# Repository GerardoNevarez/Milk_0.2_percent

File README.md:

# Milk 0.2 percent

Remix from the [2% Milk](https://github.com/Spaceboards/SpaceboardsHardware/blob/master/Keyboards/2%25%20Milk/milk_kicad.zip) by Spaceman

# BOM

- 1 - Molex 2171800001 USB-C connector [Mouser](https://www.mouser.com/ProductDetail/Molex/217180-0001?qs=DRkmTr78QAS4XYOWSgPndA%3D%3D)
- 1 - SOIC-8 ATtiny85 - [ATTINY85-20SU](https://www.mouser.com/ProductDetail/Microchip-Technology-Atmel/ATTINY85-20SU?qs=sGAEpiMZZMsJEQNpvQJiZ7QX9auzN2X%252B) 
- 1 - 0805 0.1uF ceramic cap
- 1 - 0805 4.7uF ceramic cap
- 1 - 0805 1.5k omh resistor
- 2 - 0805 5.1k omh resistors
- 2 - 0805 68 omh resistors
- 1 - 1206 500ma PolyFuse
- 2 - 0805 3.6V Zener diodes
- 1 - (optional) 6x3mm THT temporary push switch (Reset)
- 2 - (optional) 1515 RGB leds - SK6805-EC-15 [Adafruit](https://www.adafruit.com/product/4492)

Use the front and back PCB renders, to locate the location for the parts

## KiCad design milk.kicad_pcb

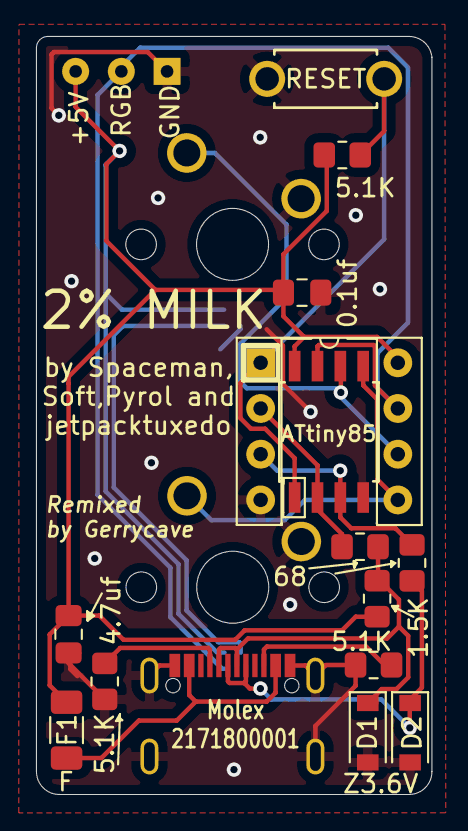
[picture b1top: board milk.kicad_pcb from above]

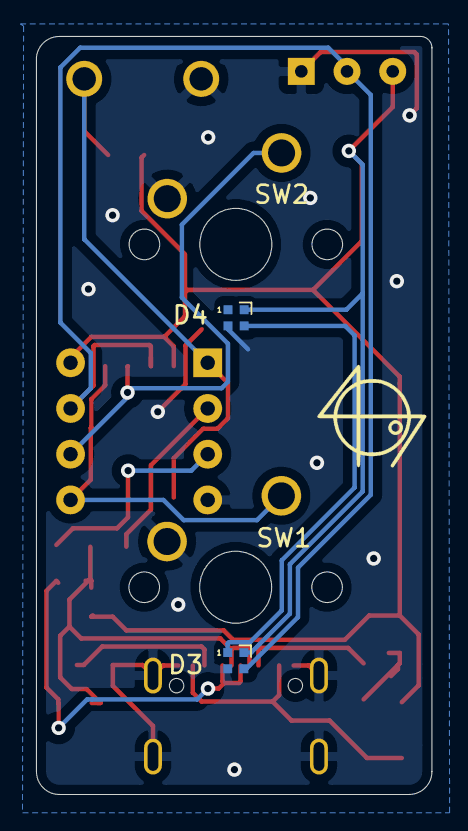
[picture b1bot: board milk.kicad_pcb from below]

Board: 2 copper layers, 22.0 x 42.1 mm, 20 parts (4 on the bottom side), 14 nets.

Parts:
C1: 0.1uf; C_0805_2012Metric_Pad1.18x1.45mm_HandSolder
C2: 4.7uf; C_0805_2012Metric_Pad1.18x1.45mm_HandSolder
D1, D2: 3.6V; D_SOD-123
D3, D4: SK6805; LED_SK6812_EC15_1.5x1.5mm
F1: Polyfuse; R_1206_3216Metric_Pad1.30x1.75mm_HandSolder
J1: USB_C_Receptacle_USB2.0; Molex_2171800001
J2: RGB; PinHeader_1x03_P2.54mm_Vertical
J3: DIP-8 Socket; DIP-8_W7.62mm_Socket
R1, R2, R6: 5.1K; R_0805_2012Metric_Pad1.20x1.40mm_HandSolder
R3, R4: 68; R_0805_2012Metric_Pad1.20x1.40mm_HandSolder
R5: 1.5K; R_0805_2012Metric_Pad1.20x1.40mm_HandSolder
SW1, SW2: SW_Push; SW_Cherry_MX_1.00u_PCB-2mm
SW3: SW_Push_Reset; ResetSW_1side
U1: ATtiny85-20SU; SOIJ-8_5.3x5.3mm_P1.27mm

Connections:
+5V: C1.1, C2.2, D3.4, D4.4, F1.1, J2.3, J3.8, R5.1, R6.2, U1.8
D+: D2.1, J1.A6, J1.B6, R4.2
D-: D1.1, J1.A7, J1.B7, R3.2, R5.2
GND: C1.2, C2.1, D1.2, D2.2, D3.2, D4.2, J1.A1, J1.B1, J1.S1, J2.1, J3.4, R1.1, R2.1, SW1.2, SW2.2, SW3.2, U1.4
unnamed: D3.1, D4.3
unnamed: J1.A5, R1.2
unnamed: J1.B5, R2.2
PB0: J3.5, SW1.1, U1.5
PB1: J3.6, SW2.1, U1.6
PB3: J3.2, R3.1, U1.2
PB4: J3.3, R4.1, U1.3
RGB: D3.3, J2.2, J3.7, U1.7
RST: J3.1, R6.1, SW3.1, U1.1
VCC: F1.2, J1.A4, J1.B4

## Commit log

2021-08-27 Initial import from SpaceboardsHardware
    https://github.com/Spaceboards/SpaceboardsHardware/blob/master/Keyboards/2%25%20Milk/milk_kicad.zip
2021-08-27 Add footprint and engineering data for Molex 2171800001 USB-C connector
2021-08-27 initial schematic and layout (fails drc)
2021-08-28 DRC ok
2021-08-28 Add programming headers (all over the place... yes)
2021-08-28 Final gerber, rendered images
2021-08-28 Add case STL from OG repo
2021-08-29 Fix pogo pin tht holes
2021-08-29 Add pull up resistor for Reset/PB5
2021-08-30 Change programming header for a DIP-8 package, compatible with ATtiny85-20PU
2021-10-19 Redo routing, add unsolderable RGB leds
2021-10-19 Fix RGB header orientation
2021-10-20 corrections to +5V line, fine-tunning tracing
2022-01-08 docs... OK... I'll do it...
2022-01-08 Add Arduino sketch
2022-01-08 more BOM details
